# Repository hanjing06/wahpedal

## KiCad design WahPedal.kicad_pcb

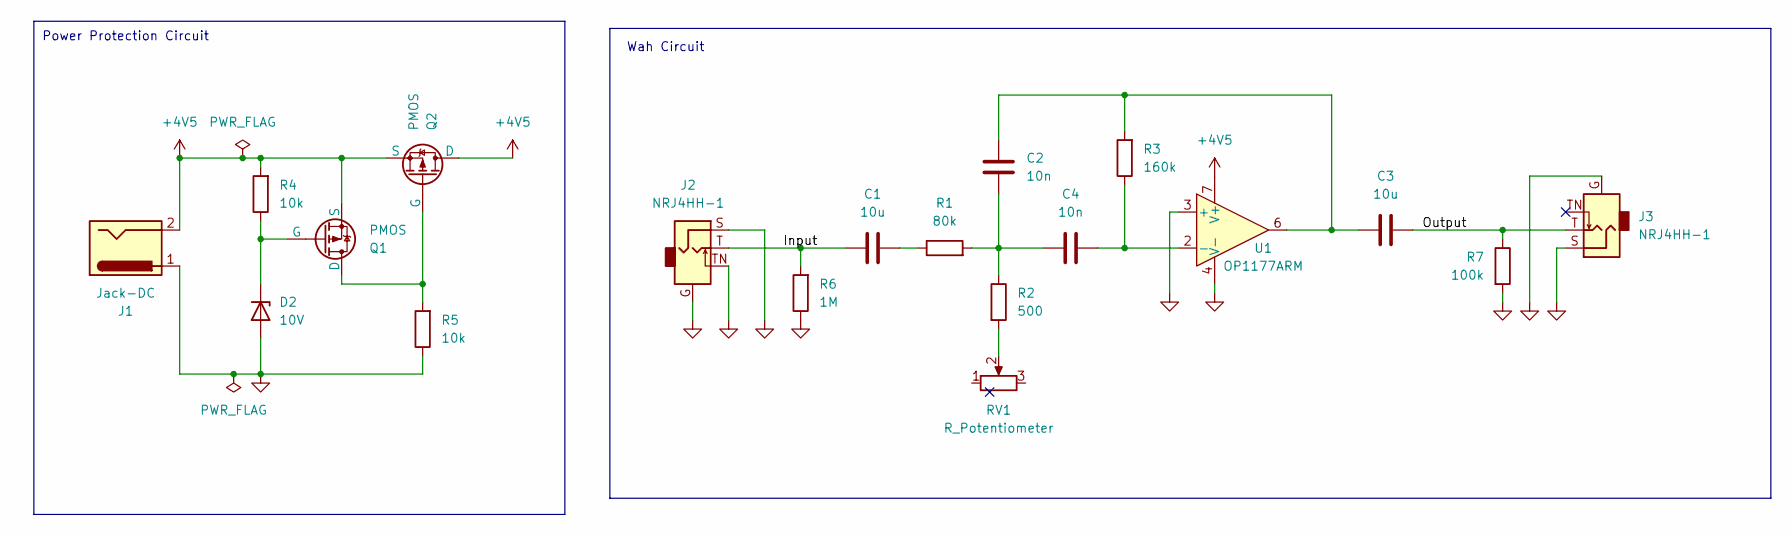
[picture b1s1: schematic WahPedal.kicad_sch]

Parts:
C1, C3: 10u; C_1206_3216Metric
C2, C4: 10n; C_1206_3216Metric
D2: 10V; Littelfuse_PolyZen-LS
J1: Jack-DC; BarrelJack_SwitchcraftConxall_RAPC10U_Horizontal
J2, J3: NRJ4HH-1; Jack_6.35mm_Neutrik_NRJ4HH-1_Horizontal
Q1, Q2: PMOS; SOT-23
R1: 80k; C_1206_3216Metric
R2: 500; C_1206_3216Metric
R3: 160k; C_1206_3216Metric
R4: 10k; C_1206_3216Metric
R5: 10k; R_1206_3216Metric
R6: 1M; R_1206_3216Metric
R7: 100k; R_1206_3216Metric
RV1: R_Potentiometer; Potentiometer_Alps_RK09Y11_Single_Horizontal
U1: OP1177ARM; MSOP-8_3x3mm_P0.65mm

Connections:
+4V5: J1.2, Q1.3 (S), Q2.1 (D), Q2.3 (S), R4.2, U1.7 (V+)
/Input: C1.2, J2.T, R6.2
/Output: C3.2, J3.T, R7.1
GND: D2.2 (A), J1.1, J2.G, J2.S, J2.TN, J3.G, J3.S, R5.1, R6.1, R7.2, U1.3 (+), U1.4 (V-)
unnamed: C1.1, R1.1
unnamed: C2.1, C3.1, R3.2, U1.6
unnamed: C2.2, C4.1, R1.2, R2.1
unnamed: D2.1 (K), Q1.2 (G), R4.1
unnamed: Q1.1 (D), Q2.2 (G), R5.2
unnamed: R2.2, RV1.2
unnamed: C4.2, R3.1, U1.2 (-)

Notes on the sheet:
Power Protection Circuit
Wah Circuit

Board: 2 copper layers, 19 parts (1 on the bottom side), 11 nets, no tracks yet.
